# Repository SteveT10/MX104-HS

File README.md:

# MX104-HS

A 104-key mechanical keyboard that I designed for myself. This keyboard currently features Hot Swappable Switches, RGB underglow, and RGB backlighting. The hardware was designed by me in KiCad and Autodesk Fusion360. The keyboard currently runs on QMK firmware, an open-sourced keyboard firmware.

## Goal
This project's goal is to act as a progressive learning project that complements my education in Computer Engineering. The first goal of this project was to familiarize myself with hardware design, where I would learn: 
- How PCBs are designed and fabricated.
- How to design circuit schematics and PCB layout in EDA software, specifically KiCad.
- How to design a basic case model in CAD software, specifically Autodesk Fusion360

<p>After verifying my hardware design and solving any potential issues, I would move onto the second goal of this project which is learn more about firmware, more specifically:</p>

- How to program C/Assembly in ARM-based MCU.
- How communication protocals such as I2C are implemented.
- Potentially more (As I have not gotten to this stage yet)

## (IN-PROGRESS) Current Version (v1.0)
This version is still in progress, most but not all components have arrived. Additionally, I need to setup QMK firmware and model the keycaps for 3D printiing them. I will document any issues or notes I find, while assemblying the keyboard.

The current version is 2 layer PCB that uses a USB-C port, a RP2040 as the brain, and 2 LED driver ICs to control the backlighting. Underglow uses addressable leds and is directly controlled by the RP2040. The firmware is currently based on QMK firmware. Some potential issues with this version are:

- The arc notches at the PCB corners are meant to secure the PCB to board, however these arcs are so small that they are effectively useless.
- Top plates are potentially incompatible, the placement of switches did not account for this at the time of design.

Front Side of PCB

Back Side of PCB (Unpopulated)

## Creating Gerbers
Most PCB fabrication places expect gerber files. Gerber files describe the layout of pads, traces, drill holes, and other geometry for each layer on the PCB. Gerber files should be uploaded in a compress zip file containing all layers. To create gerber files in KiCad v7.0:

1. Open KiCad's PCB viewer
2. Go to `File` -> `Plot`
3. Select layers and options accordingly to your fabrication shop's settings. I chose JLCPCB so I set the following options below and set all others to unchecked.
    * Include Layers:
        * F.Cu
        * B.Cu
        * F.Paste
        * B.Paste
        * F.Silkscreen
        * B.Silkscreen
        * F.Mask
        * B.Mask
        * Edge.cuts
    * `Plot reference designators`
    * `Plot footprint values`
    * `Use Protel filename extensions`
    * `Subtract soldermask from silkscreen`
    * Check zone fills before plotting.
4. Set the output directory to `project-name-gerbers`, where project name is a placeholder.
5. Click `Plot` to generate layer gerbers.
6. Click `Generate Drill files...`
7. Again, select options that match with your fabrication shop's specifications. For JLCPCB, this is:
    * Drill File Format set to Excellon.
    * Oval Holes Drill Mode is set to `Use alternate drill mode`
    * Map File Format set to `Gerber`
    * Drill Origin set to `Absolute`
    * Drill units set to `Millimeters`
    * Zeros format set to `Decimal format`
8. Click `Generate Drill File`
9. Zip up your gerber files and now it is ready for upload.

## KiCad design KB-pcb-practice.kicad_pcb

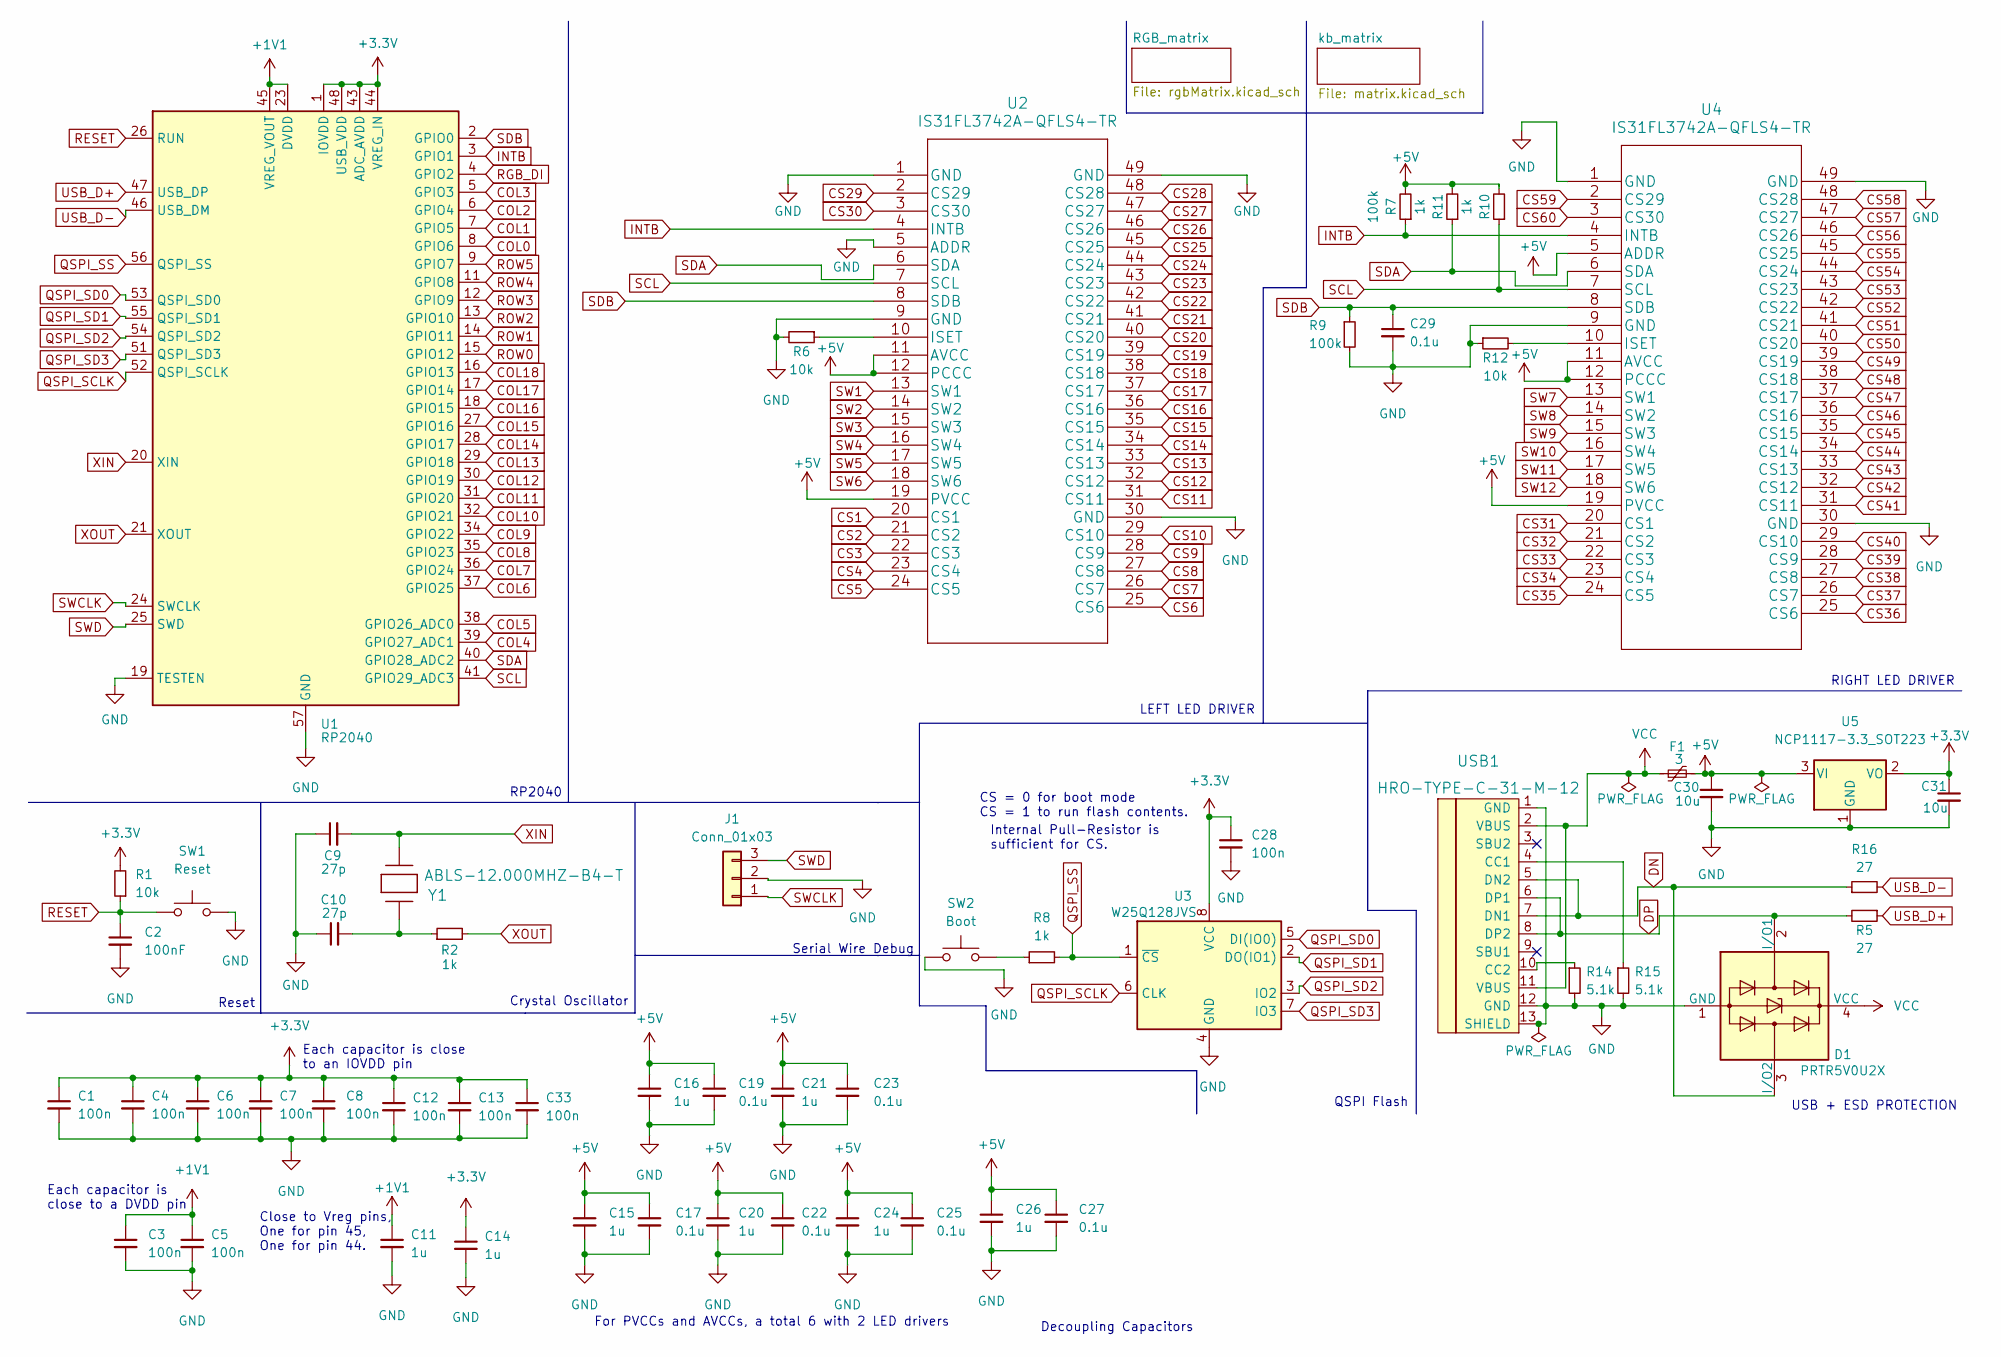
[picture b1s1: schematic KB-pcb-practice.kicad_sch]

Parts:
C1, C3, C4, C5, C6, C7, C8, C12, C13, C28, C33: 100n; C_0805_2012Metric_Pad1.18x1.45mm_HandSolder
C2: 100nF; C_0805_2012Metric_Pad1.18x1.45mm_HandSolder
C9, C10: 27p; C_0805_2012Metric_Pad1.18x1.45mm_HandSolder
C11, C14, C15, C16, C20, C21, C24, C26: 1u; C_0805_2012Metric_Pad1.18x1.45mm_HandSolder
C17, C19, C22, C23, C25, C27, C29: 0.1u; C_0805_2012Metric_Pad1.18x1.45mm_HandSolder
C30, C31: 10u; C_0805_2012Metric_Pad1.18x1.45mm_HandSolder
D1: PRTR5V0U2X; SOT-143
F1: 3; Fuse_1206_3216Metric_Pad1.42x1.75mm_HandSolder
J1: Conn_01x03; PinHeader_1x03_P2.54mm_Vertical
R1, R6, R12: 10k; R_0805_2012Metric_Pad1.20x1.40mm_HandSolder
R2, R8, R10, R11: 1k; R_0805_2012Metric_Pad1.20x1.40mm_HandSolder
R5, R16: 27; R_0805_2012Metric_Pad1.20x1.40mm_HandSolder
R7, R9: 100k; R_0805_2012Metric_Pad1.20x1.40mm_HandSolder
R14, R15: 5.1k; R_0805_2012Metric_Pad1.20x1.40mm_HandSolder
SW1: Reset; SW_SPST_SKQG_WithStem
SW2: Boot; SW_SPST_SKQG_WithStem
U1: RP2040; QFN-56-1EP_7x7mm_P0.4mm_EP3.2x3.2mm
U2, U4: IS31FL3742A-QFLS4-TR
U3: W25Q128JVS; SOIC-8_5.23x5.23mm_P1.27mm
U5: NCP1117-3.3_SOT223; SOT-223-3_TabPin2
USB1: HRO-TYPE-C-31-M-12; HRO-TYPE-C-31-M-12-HandSoldering
Y1: ABLS-12.000MHZ-B4-T

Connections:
+1V1: C3.1, C5.1, C11.1, U1.23 (DVDD), U1.45 (VREG_VOUT), U1.50 (DVDD)
+3.3V: C1.1, C4.1, C6.1, C7.1, C8.1, C12.1, C13.1, C14.1, C28.1, C31.1, C33.1, R1.2, U1.1 (IOVDD), U1.10 (IOVDD), U1.22 (IOVDD), U1.33 (IOVDD), U1.42 (IOVDD), U1.43 (ADC_AVDD), U1.44 (VREG_IN), U1.48 (USB_VDD), U1.49 (IOVDD), U3.8 (VCC), U5.2 (VO)
+5V: C15.1, C16.1, C17.1, C19.1, C20.1, C21.1, C22.1, C23.1, C24.1, C25.1, C26.1, C27.1, C30.1, F1.2, R7.2, R10.2, R11.2, U2.11 (AVCC), U2.12 (PCCC), U2.19 (PVCC), U4.5 (ADDR), U4.11 (AVCC), U4.12 (PCCC), U4.19 (PVCC), U5.3 (VI); also elsewhere on the board
COL0: U1.8 (GPIO6); also elsewhere on the board
COL1: U1.7 (GPIO5); also elsewhere on the board
COL2: U1.6 (GPIO4); also elsewhere on the board
COL3: U1.5 (GPIO3); also elsewhere on the board
COL4: U1.39 (GPIO27_ADC1); also elsewhere on the board
COL5: U1.38 (GPIO26_ADC0); also elsewhere on the board
COL6: U1.37 (GPIO25); also elsewhere on the board
COL7: U1.36 (GPIO24); also elsewhere on the board
COL8: U1.35 (GPIO23); also elsewhere on the board
COL9: U1.34 (GPIO22); also elsewhere on the board
COL10: U1.32 (GPIO21); also elsewhere on the board
COL11: U1.31 (GPIO20); also elsewhere on the board
COL12: U1.30 (GPIO19); also elsewhere on the board
COL13: U1.29 (GPIO18); also elsewhere on the board
COL14: U1.28 (GPIO17); also elsewhere on the board
COL15: U1.27 (GPIO16); also elsewhere on the board
COL16: U1.18 (GPIO15); also elsewhere on the board
COL17: U1.17 (GPIO14); also elsewhere on the board
COL18: U1.16 (GPIO13); also elsewhere on the board
CS1: U2.20 (CS1); also elsewhere on the board
CS2: U2.21 (CS2); also elsewhere on the board
CS3: U2.22 (CS3); also elsewhere on the board
CS4: U2.23 (CS4); also elsewhere on the board
CS5: U2.24 (CS5); also elsewhere on the board
CS6: U2.25 (CS6); also elsewhere on the board
CS7: U2.26 (CS7); also elsewhere on the board
CS8: U2.27 (CS8); also elsewhere on the board
CS9: U2.28 (CS9); also elsewhere on the board
CS10: U2.29 (CS10); also elsewhere on the board
CS11: U2.31 (CS11); also elsewhere on the board
CS12: U2.32 (CS12); also elsewhere on the board
CS13: U2.33 (CS13); also elsewhere on the board
CS14: U2.34 (CS14); also elsewhere on the board
CS15: U2.35 (CS15); also elsewhere on the board
CS16: U2.36 (CS16); also elsewhere on the board
CS17: U2.37 (CS17); also elsewhere on the board
CS18: U2.38 (CS18); also elsewhere on the board
CS19: U2.39 (CS19); also elsewhere on the board
CS20: U2.40 (CS20); also elsewhere on the board
CS21: U2.41 (CS21); also elsewhere on the board
CS22: U2.42 (CS22); also elsewhere on the board
CS23: U2.43 (CS23); also elsewhere on the board
CS24: U2.44 (CS24); also elsewhere on the board
CS25: U2.45 (CS25); also elsewhere on the board
CS26: U2.46 (CS26); also elsewhere on the board
CS27: U2.47 (CS27); also elsewhere on the board
CS28: U2.48 (CS28); also elsewhere on the board
CS29: U2.2 (CS29); also elsewhere on the board
CS30: U2.3 (CS30); also elsewhere on the board
CS31: U4.20 (CS1); also elsewhere on the board
CS32: U4.21 (CS2); also elsewhere on the board
CS33: U4.22 (CS3); also elsewhere on the board
CS34: U4.23 (CS4); also elsewhere on the board
CS35: U4.24 (CS5); also elsewhere on the board
CS36: U4.25 (CS6); also elsewhere on the board
CS37: U4.26 (CS7); also elsewhere on the board
CS38: U4.27 (CS8); also elsewhere on the board
CS39: U4.28 (CS9); also elsewhere on the board
CS40: U4.29 (CS10); also elsewhere on the board
CS41: U4.31 (CS11); also elsewhere on the board
CS42: U4.32 (CS12); also elsewhere on the board
CS43: U4.33 (CS13); also elsewhere on the board
CS44: U4.34 (CS14); also elsewhere on the board
CS45: U4.35 (CS15); also elsewhere on the board
CS46: U4.36 (CS16); also elsewhere on the board
CS47: U4.37 (CS17); also elsewhere on the board
CS48: U4.38 (CS18); also elsewhere on the board
CS49: U4.39 (CS19); also elsewhere on the board
CS50: U4.40 (CS20); also elsewhere on the board
CS51: U4.41 (CS21); also elsewhere on the board
CS52: U4.42 (CS22); also elsewhere on the board
CS53: U4.43 (CS23); also elsewhere on the board
CS54: U4.44 (CS24); also elsewhere on the board
CS55: U4.45 (CS25); also elsewhere on the board
CS56: U4.46 (CS26); also elsewhere on the board
CS57: U4.47 (CS27); also elsewhere on the board
CS58: U4.48 (CS28); also elsewhere on the board
CS59: U4.2 (CS29); also elsewhere on the board
CS60: U4.3 (CS30); also elsewhere on the board
DN: D1.3 (I/O2), R16.1, USB1.5 (DN2), USB1.7 (DN1)
DP: D1.2 (I/O1), R5.2, USB1.6 (DP1), USB1.8 (DP2)
GND: C1.2, C2.2, C3.2, C4.2, C5.2, C6.2, C7.2, C8.2, C9.1, C10.1, C11.2, C12.2, C13.2, C14.2, C15.2, C16.2, C17.2, C19.2, C20.2, C21.2, C22.2, C23.2, C24.2, C25.2, C26.2, C27.2, C28.2, C29.2, C30.2, C31.2, C33.2, D1.1 (GND), J1.2, R6.2, R9.2, R12.1, R14.2, R15.2, SW1.2, SW2.1, U1.19 (TESTEN), U1.57 (GND), U2.1 (GND), U2.5 (ADDR), U2.9 (GND), U2.30 (GND), U2.49 (GND), U3.4 (GND), U4.1 (GND), U4.9 (GND), U4.30 (GND), U4.49 (GND), U5.1 (GND), USB1.1 (GND), USB1.12 (GND), USB1.13 (SHIELD); also elsewhere on the board
INTB: R7.1, U1.3 (GPIO1), U2.4 (INTB), U4.4 (INTB)
unnamed: C10.2, R2.1, Y1.1
unnamed: R8.1, SW2.2
unnamed: R6.1, U2.10 (ISET)
unnamed: R12.2, U4.10 (ISET)
unnamed: R15.1, USB1.4 (CC1)
unnamed: R14.1, USB1.10 (CC2)
QSPI_SCLK: U1.52 (QSPI_SCLK), U3.6 (CLK)
QSPI_SD0: U1.53 (QSPI_SD0), U3.5 (DI(IO0))
QSPI_SD1: U1.55 (QSPI_SD1), U3.2 (DO(IO1))
QSPI_SD2: U1.54 (QSPI_SD2), U3.3 (IO2)
QSPI_SD3: U1.51 (QSPI_SD3), U3.7 (IO3)
QSPI_SS: R8.2, U1.56 (QSPI_SS), U3.1 (~CS)
RESET: C2.1, R1.1, SW1.1, U1.26 (RUN)
RGB_DI: U1.4 (GPIO2); also elsewhere on the board
ROW0: U1.15 (GPIO12); also elsewhere on the board
ROW1: U1.14 (GPIO11); also elsewhere on the board
ROW2: U1.13 (GPIO10); also elsewhere on the board
ROW3: U1.12 (GPIO9); also elsewhere on the board
ROW4: U1.11 (GPIO8); also elsewhere on the board
ROW5: U1.9 (GPIO7); also elsewhere on the board
SCL: R10.1, U1.41 (GPIO29_ADC3), U2.7 (SCL), U4.7 (SCL)
SDA: R11.1, U1.40 (GPIO28_ADC2), U2.6 (SDA), U4.6 (SDA)
SDB: C29.1, R9.1, U1.2 (GPIO0), U2.8 (SDB), U4.8 (SDB)
SW1: U2.13 (SW1); also elsewhere on the board
SW2: U2.14 (SW2); also elsewhere on the board
SW3: U2.15 (SW3); also elsewhere on the board
SW4: U2.16 (SW4); also elsewhere on the board
SW5: U2.17 (SW5); also elsewhere on the board
SW6: U2.18 (SW6); also elsewhere on the board
SW7: U4.13 (SW1); also elsewhere on the board
SW8: U4.14 (SW2); also elsewhere on the board
SW9: U4.15 (SW3); also elsewhere on the board
SW10: U4.16 (SW4); also elsewhere on the board
SW11: U4.17 (SW5); also elsewhere on the board
SW12: U4.18 (SW6); also elsewhere on the board
SWCLK: J1.1, U1.24 (SWCLK)
SWD: J1.3, U1.25 (SWD)
USB_D+: R5.1, U1.47 (USB_DP)
USB_D-: R16.2, U1.46 (USB_DM)
VCC: D1.4 (VCC), F1.1, USB1.2 (VBUS), USB1.11 (VBUS)
XIN: C9.2, U1.20 (XIN), Y1.2
XOUT: R2.2, U1.21 (XOUT)

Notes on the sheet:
LEFT LED DRIVER
Close to Vreg pins, One for pin 45, One for pin 44.
RP2040
RIGHT LED DRIVER
Internal Pull-Resistor is sufficient for CS.
Decoupling Capacitors
Serial Wire Debug
Each capacitor is close to an IOVDD pin
Crystal Oscillator
CS = 0 for boot mode CS = 1 to run flash contents.
Reset
USB + ESD PROTECTION
Each capacitor is close to a DVDD pin
QSPI Flash
For PVCCs and AVCCs, a total 6 with 2 LED drivers

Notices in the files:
parts and their libraries:
Copyright 2016 Accelerated Designs. All rights reserved.
Copyright 2021 Accelerated Designs. All rights reserved.
